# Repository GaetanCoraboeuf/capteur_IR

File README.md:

# capteur_IR

Le but de ce projet est de concevoir un capteur de détection de mouvement par infrarouges. Cette solution est modulable et scalable en plus de son coût de fabrication faible.

## Table des Matières

- [Description](#description)
- [Hardware](#hardware)
- [Software](#software)
- [Évolutions](#évolutions)
- [Contributeurs](#contributeurs)

## Description

Il est composé de deux grande parties:
 - Electronique (ESP32 + capteur IR LHI968)
 - Software (code C++ + dashboard avec base de données)

Ce projet a été fait par des étudiants.

## Hardware

La carte électronique est conçu pour être un sheld pour une Esp32 devkit V1.
On a utilisé KiCad pour la concevoir et générer le modèle 3D.
Et on l'a réalisé en prototypage rapide sur CNC.

Voici le schéma électronique :

Et voici la réalisation final :

## Software

Ce code permet de se connecter à une base de données influxDB via une requête POST.
De notre côté on a choisi d'héberger cette base de données sur une Raspberry Pi et de l'exploiter avec Grafana.

Ce code envoie simplement la tesion du capteur toutes les 100ms à la base de données et tente une reconection au Wi-Fi chaque fois qui pert le signal.

## Boitier

Nous avons aussi conçu un boitier pour le capteur. Il est imprimé en 3D et permet d'intégrer tous les composants de manière esthétique et fonctionnelle. (merci à BHP pour la conception du boitier)

## Évolutions

- [x] Remplacement du convertisseur boost par une pile 9V (ce convertisseur n'est pas recomandé)
- [ ] Lecture de la tension de batterie avec un pont diviseur
- [ ] Scan des periphériques Bluethooth à proximité (distinction autorisé/non-autorisé)
- [ ] Detection sonore, bruit ambiant
- [ ] Camera avec intégration IA (OpenCV)
- [ ] Utiliser l'horloge temps réel de l'ESP32 pour horodater les valeurs grace à un serveur de temps (plus précis)
- [ ] Mettre en place un buffer en cas de coupure de connection pour ne pas perdre de valeurs

## Contributeurs

Ambroise Nedey-Crettaz <br />
Gaëtan Corabœuf

Sur la proposition de : <br />
M.Dumas

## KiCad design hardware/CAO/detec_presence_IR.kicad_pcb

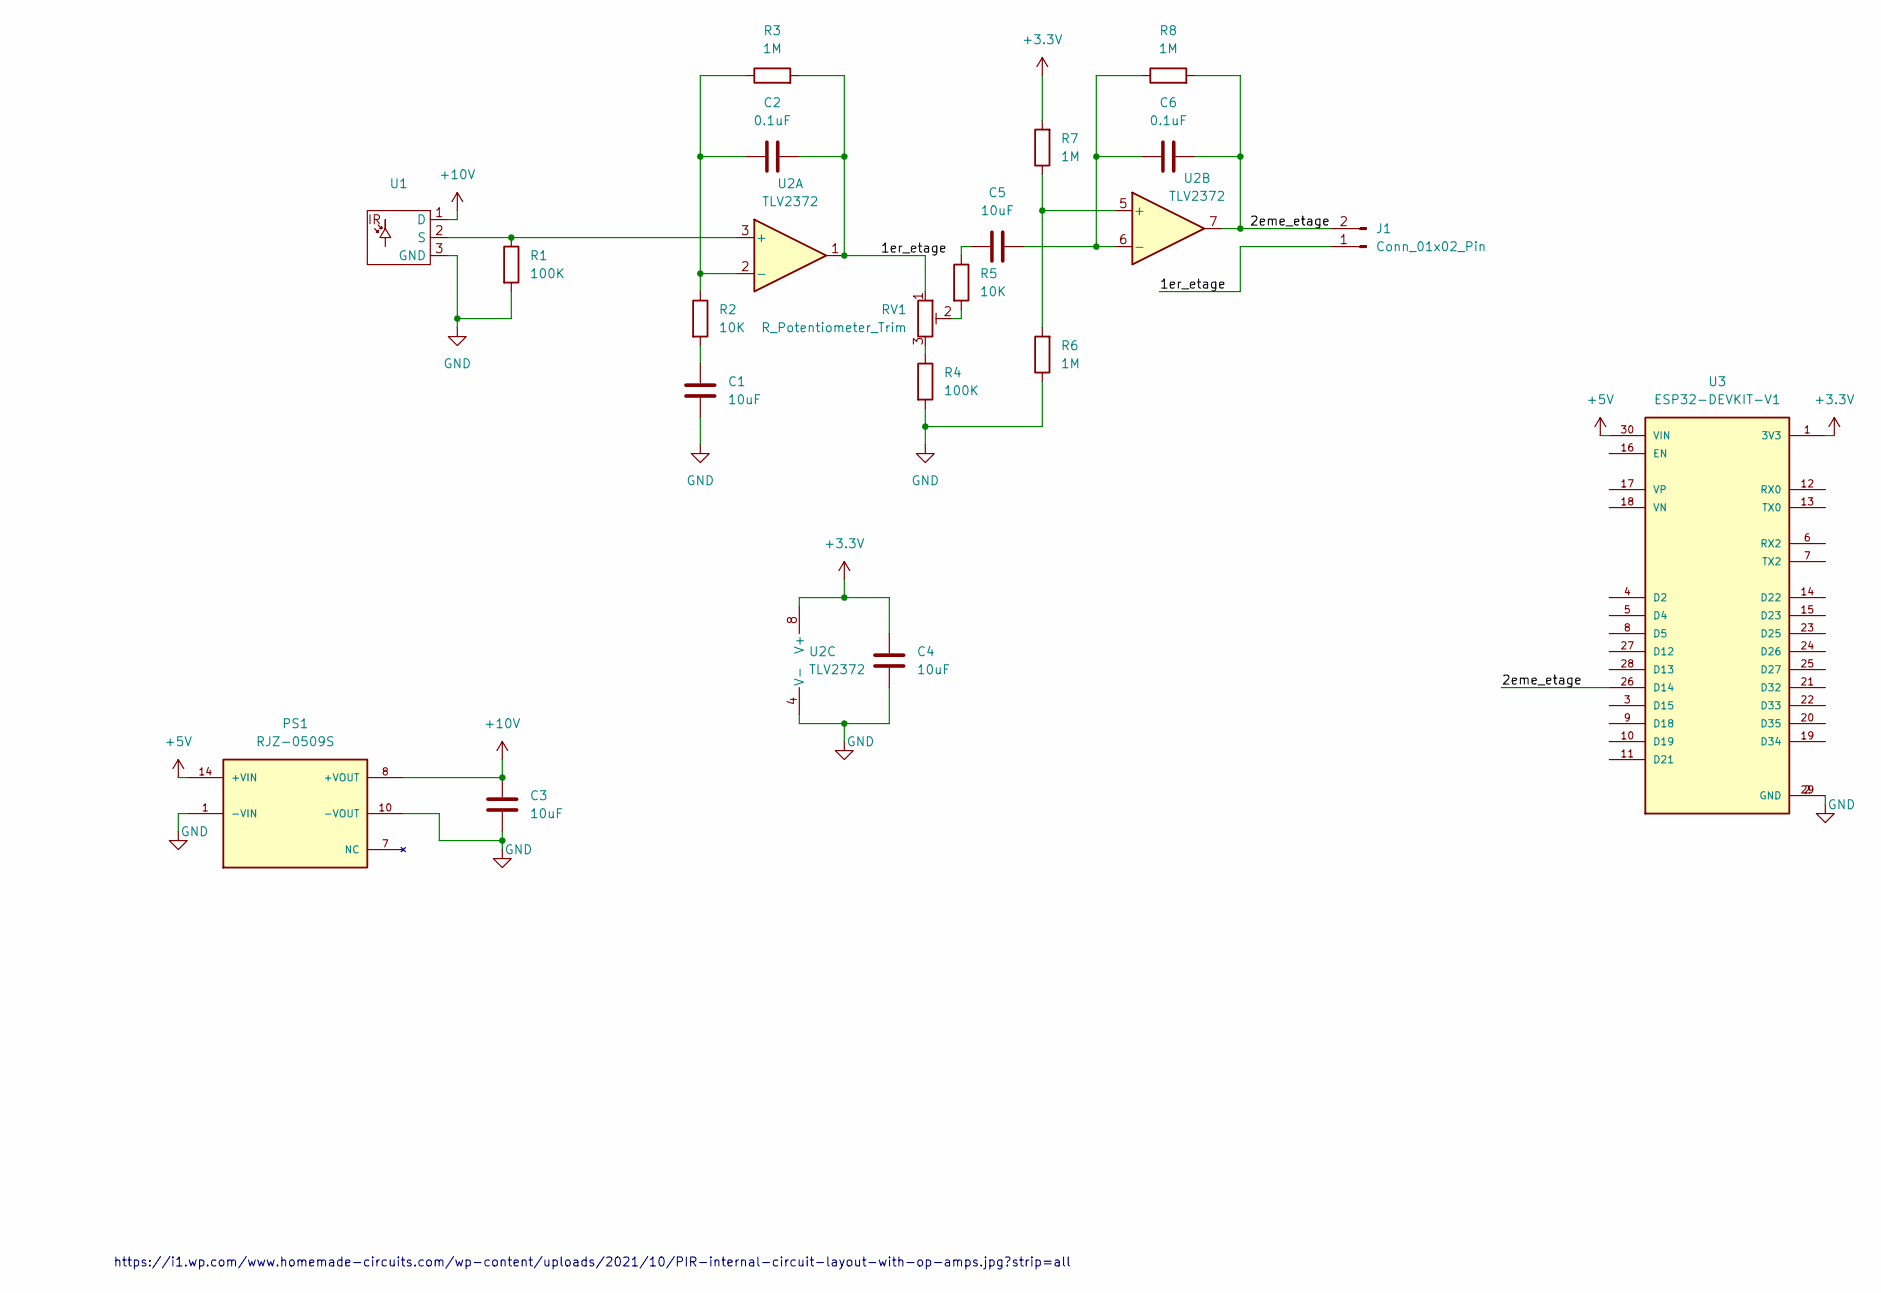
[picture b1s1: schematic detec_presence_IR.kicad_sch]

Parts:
C1, C3, C4, C5: 10uF; C_0805_2012Metric_Pad1.18x1.45mm_HandSolder
C2, C6: 0.1uF; C_0805_2012Metric_Pad1.18x1.45mm_HandSolder
J1: Conn_01x02_Pin; PinHeader_1x02_P2.54mm_Vertical
PS1: RJZ-0509S; RJZ-0509S_CONV_RJZ-0509S; PARTREV 1
R1, R4: 100K; R_0805_2012Metric_Pad1.20x1.40mm_HandSolder
R2, R5: 10K; R_0805_2012Metric_Pad1.20x1.40mm_HandSolder
R3, R6, R7, R8: 1M; R_0805_2012Metric_Pad1.20x1.40mm_HandSolder
RV1: R_Potentiometer_Trim; Potentiometer_Vishay_T93YA_Vertical
U1: TO254P940H1930-3
U2: TLV2372; SOIC-8_3.9x4.9mm_P1.27mm
U3: ESP32-DEVKIT-V1; ESP32-DEVKIT-V1_MODULE_ESP32_DEVKIT_V1; PARTREV N/A

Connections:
+3.3V: C4.1, R7.2, U2.8 (V+), U3.1 (3V3)
+5V: PS1.14 (+VIN), U3.30 (VIN)
+10V: C3.1, PS1.8 (+VOUT), U1.1 (D)
/1er_etage: C2.2, J1.1, R3.2, RV1.1, U2.1
/2eme_etage: C6.2, J1.2, R8.2, U2.7, U3.26 (D14)
GND: C1.2, C3.2, C4.2, PS1.1 (-VIN), PS1.10 (-VOUT), R1.2, R4.2, R6.1, U1.3 (GND), U2.4 (V-), U3.2 (GND), U3.29 (GND)
unnamed: C1.1, R2.2
unnamed: C5.1, R5.1
unnamed: R4.1, RV1.3
unnamed: R5.2, RV1.2
unnamed: R1.1, U1.2 (S), U2.3 (+)
unnamed: C2.1, R2.1, R3.1, U2.2 (-)
unnamed: R6.2, R7.1, U2.5 (+)
unnamed: C5.2, C6.1, R8.1, U2.6 (-)

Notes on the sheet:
https://i1.wp.com/www.homemade-circuits.com/wp-content/uploads/2021/10/PIR-internal-circuit-layout-with-op-amps.jpg?strip=all

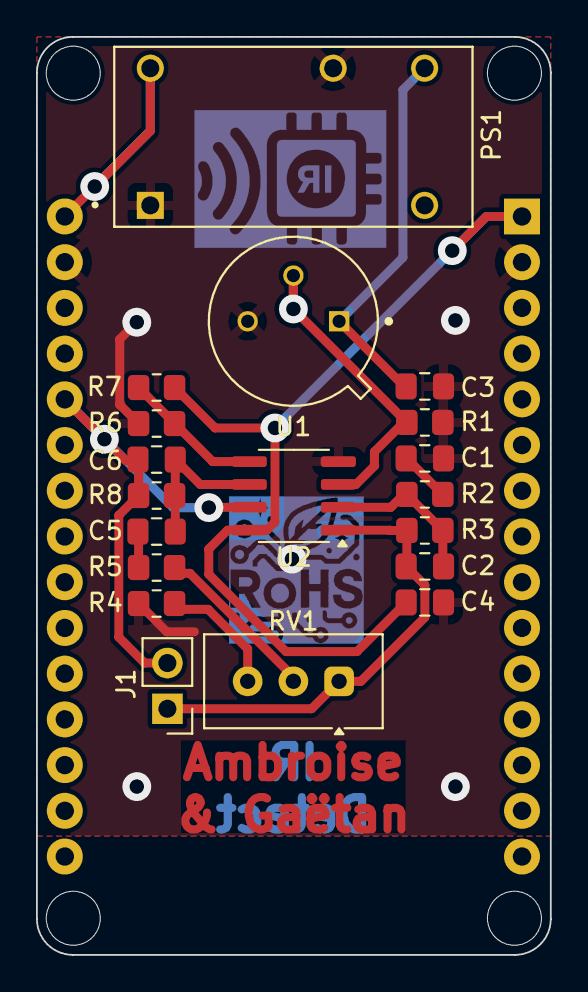
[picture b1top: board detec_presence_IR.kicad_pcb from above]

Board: 2 copper layers, 28.6 x 51.0 mm, 20 parts (1 on the bottom side), 14 nets.

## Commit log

2025-05-12 lecture analogique
2025-05-18 dev-ia
2025-05-18 mag_wifi_pass
2025-05-18 code_fonctionel
2025-05-18 merge
2025-05-19 ajout hard
2025-05-19 readme
2025-05-19 test
2025-05-19 test 2
2025-05-19 fin de journée
2025-05-25 mage readme + boitier
2025-05-25 mag link
2025-05-25 espace
2025-05-25 case afichage correct
